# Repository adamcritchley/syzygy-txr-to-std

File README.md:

# syzygy-txr-to-std
SYZYGY Adapter Board from TXR QSH to STD QSE

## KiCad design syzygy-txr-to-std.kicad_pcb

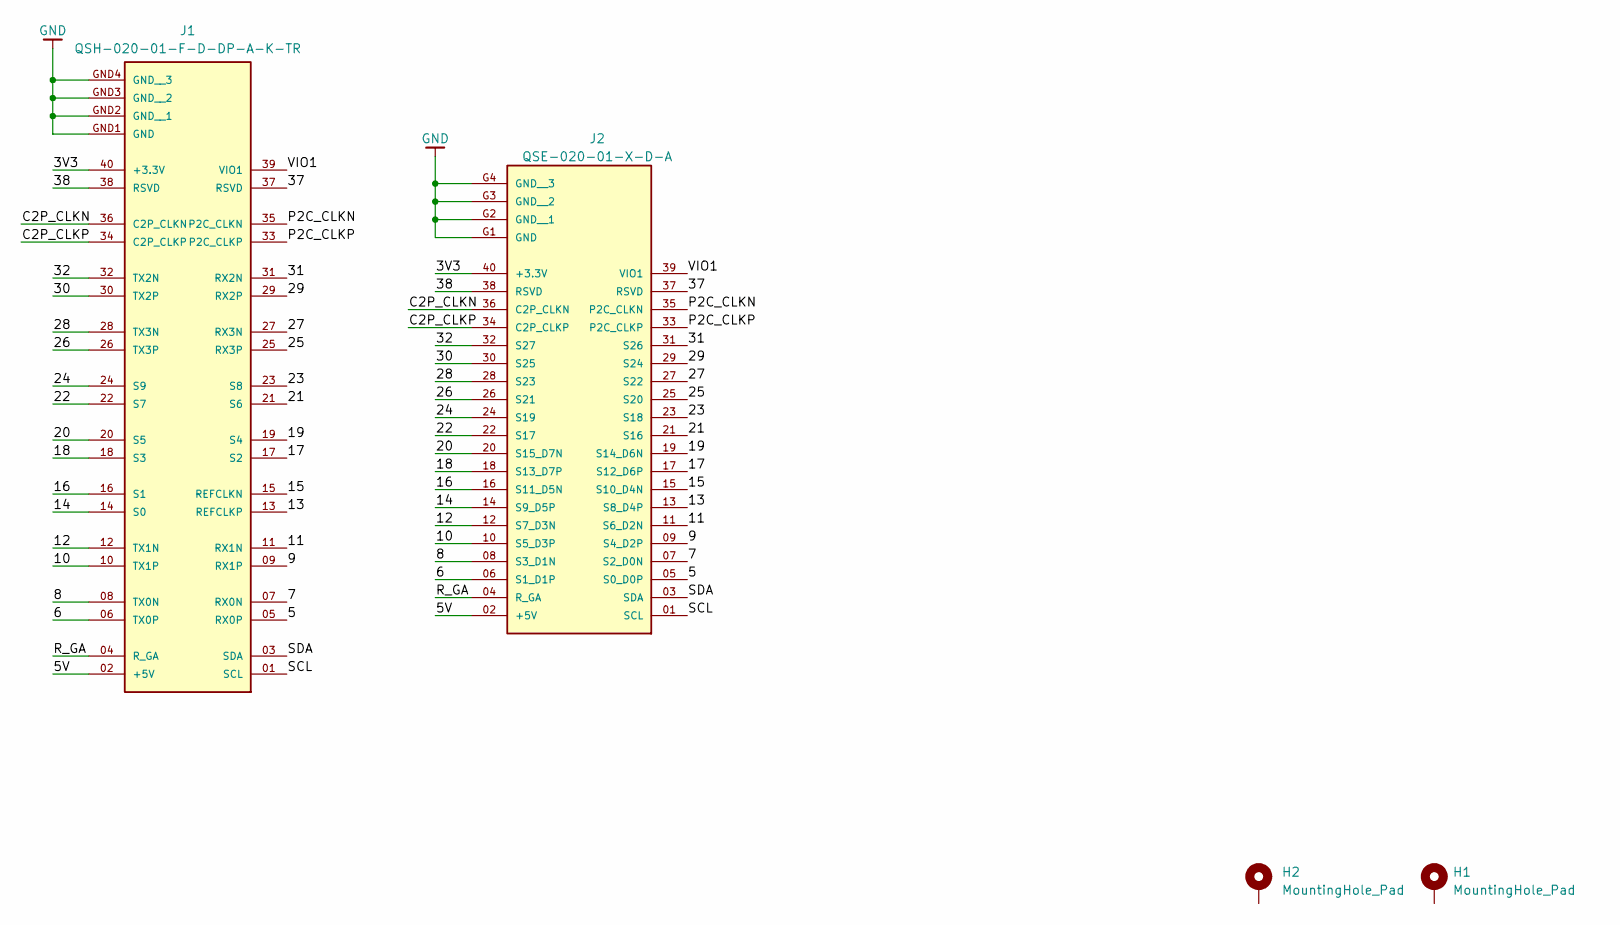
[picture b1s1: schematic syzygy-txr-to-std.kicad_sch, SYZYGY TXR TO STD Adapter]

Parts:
H1, H2: MountingHole_Pad; MountingHole_3.2mm_M3_Pad
J1: QSH-020-01-F-D-DP-A-K-TR; SAMTEC_QSH-020-01-X-D-DP; PARTREV M
J2: QSE-020-01-X-D-A; SAMTEC_QSE-020-01-X-D-A; PARTREV N

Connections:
/3V3: J1.40 (+3.3V), J2.40 (+3.3V)
/5: J1.05 (RX0P), J2.05 (S0_D0P)
/5V: J1.02 (+5V), J2.02 (+5V)
/6: J1.06 (TX0P), J2.06 (S1_D1P)
/7: J1.07 (RX0N), J2.07 (S2_D0N)
/8: J1.08 (TX0N), J2.08 (S3_D1N)
/9: J1.09 (RX1P), J2.09 (S4_D2P)
/10: J1.10 (TX1P), J2.10 (S5_D3P)
/11: J1.11 (RX1N), J2.11 (S6_D2N)
/12: J1.12 (TX1N), J2.12 (S7_D3N)
/13: J1.13 (REFCLKP), J2.13 (S8_D4P)
/14: J1.14 (S0), J2.14 (S9_D5P)
/15: J1.15 (REFCLKN), J2.15 (S10_D4N)
/16: J1.16 (S1), J2.16 (S11_D5N)
/17: J1.17 (S2), J2.17 (S12_D6P)
/18: J1.18 (S3), J2.18 (S13_D7P)
/19: J1.19 (S4), J2.19 (S14_D6N)
/20: J1.20 (S5), J2.20 (S15_D7N)
/21: J1.21 (S6), J2.21 (S16)
/22: J1.22 (S7), J2.22 (S17)
/23: J1.23 (S8), J2.23 (S18)
/24: J1.24 (S9), J2.24 (S19)
/25: J1.25 (RX3P), J2.25 (S20)
/26: J1.26 (TX3P), J2.26 (S21)
/27: J1.27 (RX3N), J2.27 (S22)
/28: J1.28 (TX3N), J2.28 (S23)
/29: J1.29 (RX2P), J2.29 (S24)
/30: J1.30 (TX2P), J2.30 (S25)
/31: J1.31 (RX2N), J2.31 (S26)
/32: J1.32 (TX2N), J2.32 (S27)
/37: J1.37 (RSVD), J2.37 (RSVD)
/38: J1.38 (RSVD), J2.38 (RSVD)
/C2P_CLKN: J1.36 (C2P_CLKN), J2.36 (C2P_CLKN)
/C2P_CLKP: J1.34 (C2P_CLKP), J2.34 (C2P_CLKP)
/P2C_CLKN: J1.35 (P2C_CLKN), J2.35 (P2C_CLKN)
/P2C_CLKP: J1.33 (P2C_CLKP), J2.33 (P2C_CLKP)
/R_GA: J1.04 (R_GA), J2.04 (R_GA)
/SCL: J1.01 (SCL), J2.01 (SCL)
/SDA: J1.03 (SDA), J2.03 (SDA)
/VIO1: J1.39 (VIO1), J2.39 (VIO1)
GND: H1.1, H2.1, J1.GND1 (GND), J1.GND2 (GND__1), J1.GND3 (GND__2), J1.GND4 (GND__3), J2.G1 (GND), J2.G2 (GND__1), J2.G3 (GND__2), J2.G4 (GND__3)

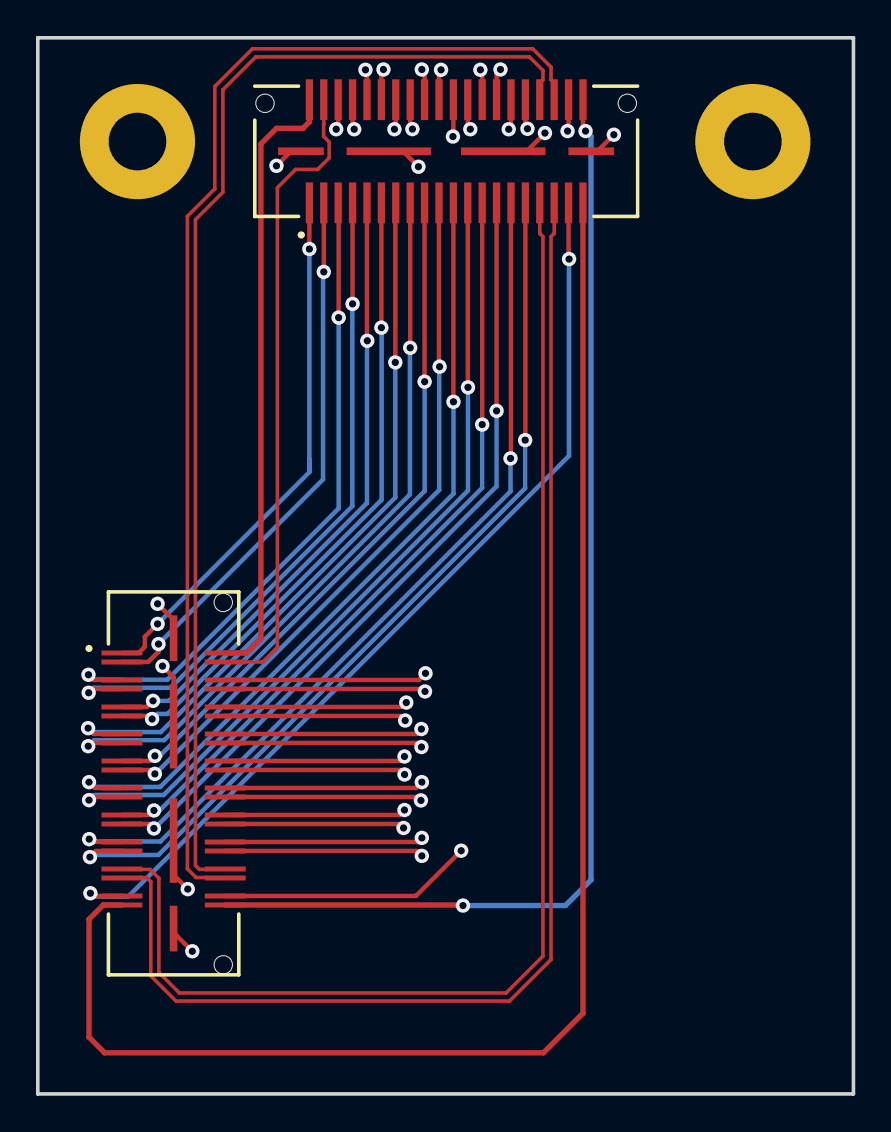
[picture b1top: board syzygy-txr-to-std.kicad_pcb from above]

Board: 4 copper layers, 45.3 x 58.7 mm, 4 parts (0 on the bottom side), 41 nets.
